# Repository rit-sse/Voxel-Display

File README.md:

RIT/SSE - Voxel Display Project
---

Society of Software Engineers' project to build a 3D display using voxels in a real 3D space.

Hi there? Are you here to try out our 3D Browser-based voxel simulator? [You can find it here.](http://rit-sse.github.io/Voxel-Display/)

The browser simulator is pretty cool - you can use your mouse and arrow keys to navigate around the 3d view. 

At first, the display is simply off. You can begin toggling voxels as you please by using the controls in the upper left.

You'll notice the "browse" button - this file selector lets you run an application with the display. Example applications can be found [in the apps folder.](https://github.com/rit-sse/Voxel-Display/tree/gh-pages/apps)

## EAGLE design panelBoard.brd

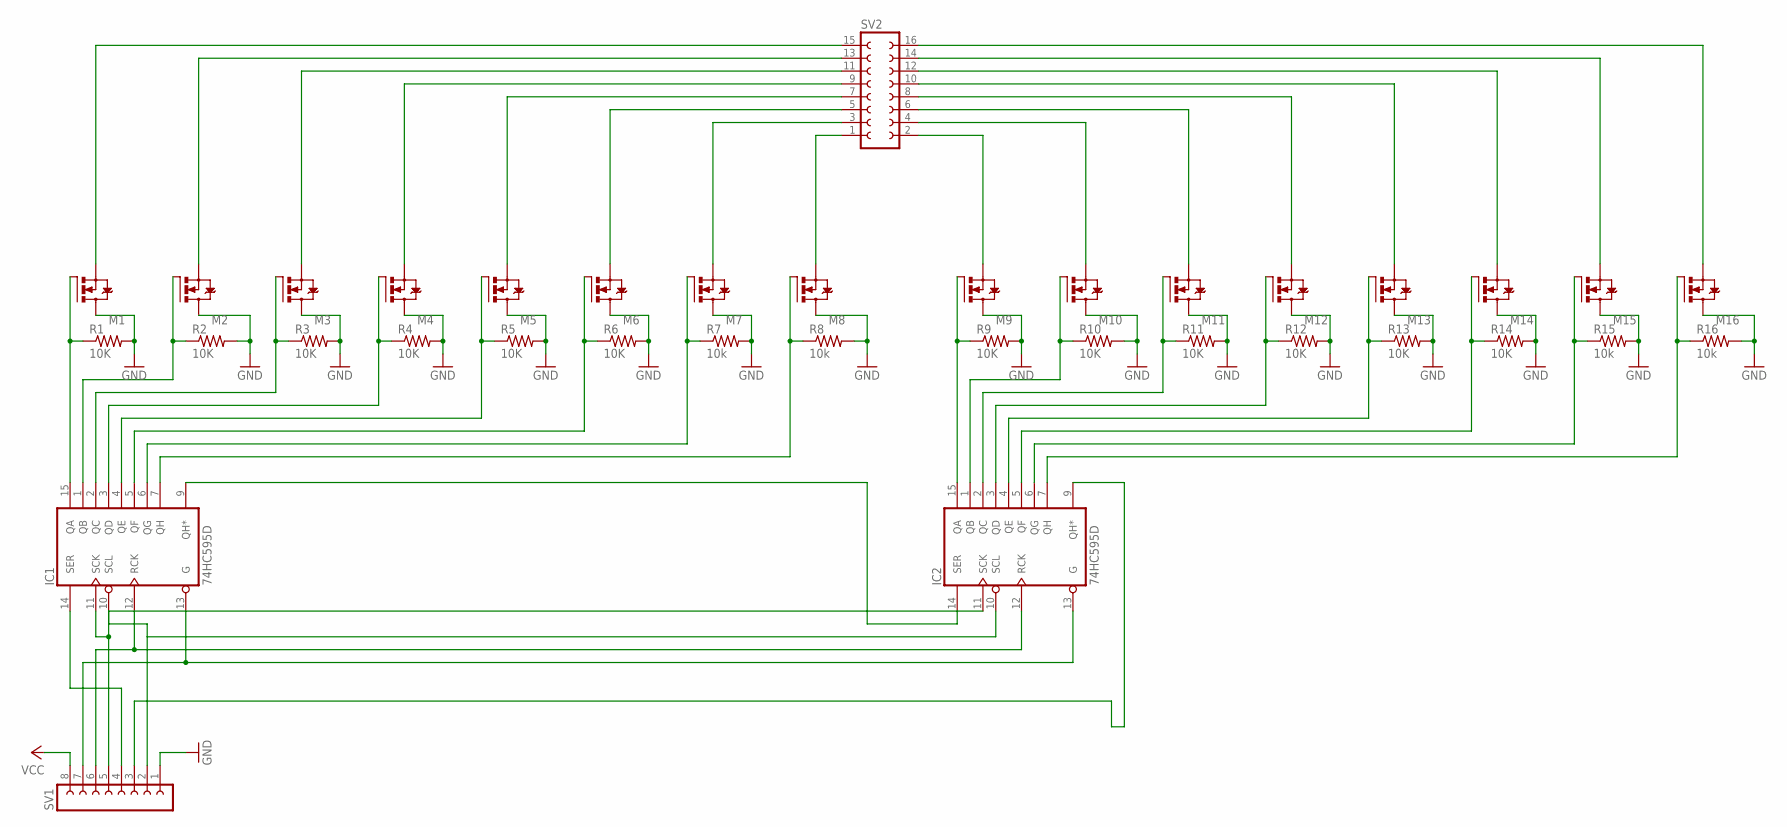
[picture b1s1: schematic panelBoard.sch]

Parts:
IC1, IC2: 74HC595D; SO16
M1, M2, M3, M4, M5, M6, M7, M8, M9, M10, M11, M12, M13, M14, M15, M16: 2N7000; TO92D-
R1, R2, R3, R4, R5, R6, R9, R10, R11, R12, R13, R14: 10K; R0603
R7, R8, R15, R16: 10k; R0603
SV1: FE08-1; FE08
SV2: FE08-2

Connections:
GND: IC1.8 (GND), IC2.8 (GND), M1.3 (D), M2.3 (D), M3.3 (D), M4.3 (D), M5.3 (D), M6.3 (D), M7.3 (D), M8.3 (D), M9.3 (D), M10.3 (D), M11.3 (D), M12.3 (D), M13.3 (D), M14.3 (D), M15.3 (D), M16.3 (D), R1.2, R2.2, R3.2, R4.2, R5.2, R6.2, R7.2, R8.2, R9.2, R10.2, R11.2, R12.2, R13.2, R14.2, R15.2, R16.2, SV1.1
unnamed: M1.1 (S), SV2.15
unnamed: M2.1 (S), SV2.13
unnamed: M3.1 (S), SV2.11
unnamed: M4.1 (S), SV2.9
unnamed: M5.1 (S), SV2.7
unnamed: M6.1 (S), SV2.5
unnamed: M7.1 (S), SV2.3
unnamed: M8.1 (S), SV2.1
unnamed: IC1.7 (QH), M8.2 (G), R8.1
unnamed: IC1.15 (QA), M1.2 (G), R1.1
unnamed: IC1.1 (QB), M2.2 (G), R2.1
unnamed: IC1.2 (QC), M3.2 (G), R3.1
unnamed: IC1.3 (QD), M4.2 (G), R4.1
unnamed: IC1.4 (QE), M5.2 (G), R5.1
unnamed: IC1.5 (QF), M6.2 (G), R6.1
unnamed: IC1.13 (G), IC2.13 (G), SV1.7
unnamed: IC1.6 (QG), M7.2 (G), R7.1
unnamed: IC1.12 (RCK), IC2.12 (RCK), SV1.6
unnamed: IC1.11 (SCK), IC2.11 (SCK), SV1.5
unnamed: IC1.14 (SER), SV1.4
unnamed: IC1.9 (QH*), IC2.14 (SER)
unnamed: IC1.10 (SCL), IC2.10 (SCL), SV1.2
unnamed: M9.1 (S), SV2.2
unnamed: M10.1 (S), SV2.4
unnamed: M11.1 (S), SV2.6
unnamed: M12.1 (S), SV2.8
unnamed: M13.1 (S), SV2.10
unnamed: M14.1 (S), SV2.12
unnamed: M15.1 (S), SV2.14
unnamed: M16.1 (S), SV2.16
unnamed: IC2.15 (QA), M9.2 (G), R9.1
unnamed: IC2.1 (QB), M10.2 (G), R10.1
unnamed: IC2.2 (QC), M11.2 (G), R11.1
unnamed: IC2.3 (QD), M12.2 (G), R12.1
unnamed: IC2.4 (QE), M13.2 (G), R13.1
unnamed: IC2.5 (QF), M14.2 (G), R14.1
unnamed: IC2.7 (QH), M16.2 (G), R16.1
unnamed: IC2.6 (QG), M15.2 (G), R15.1
unnamed: IC2.9 (QH*), SV1.3
VCC: IC1.16 (VCC), IC2.16 (VCC), SV1.8

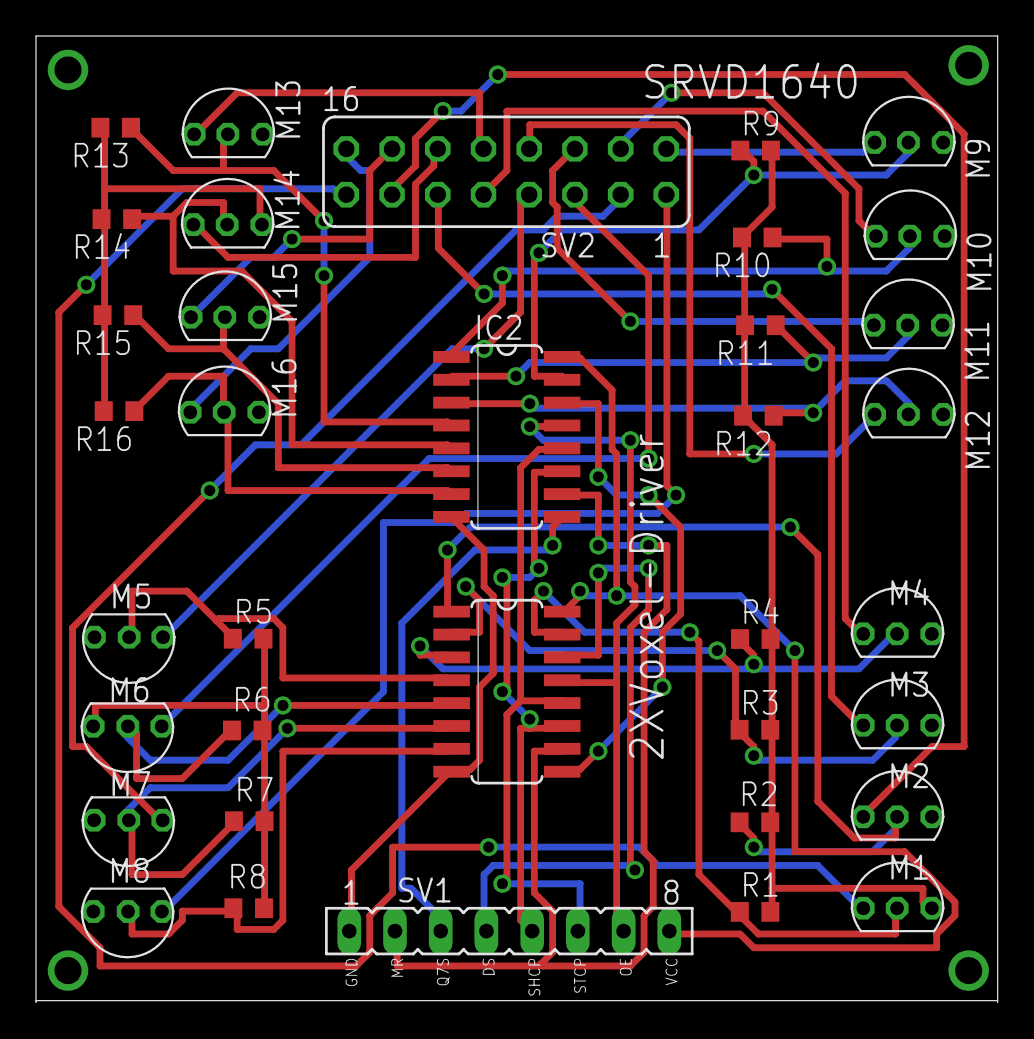
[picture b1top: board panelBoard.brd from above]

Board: 2 copper layers, 53.4 x 53.7 mm, 36 parts (0 on the bottom side), 41 nets.

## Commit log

2014-02-25 add README
2014-03-02 added Mock TkVoxelDisplay
2014-03-08 add waffle.io badge
2014-03-08 moved TkPreview to TkMockView
2014-03-08 added git ignore for TkMockView
2014-03-08 added documents for git-wiki and git-issues
2014-03-09 Added In-Progress Badge
2014-03-12 added minutes for 3_11_14
2014-03-12 updated name and refrence image
2014-03-17 Add barebones processing project
2014-03-17 Add a bunch of deps (probably more than we need)
2014-03-17 Simple 3d example
2014-03-18 added translate example, WITH COLOR\!
2014-03-18 Non-working, star code
2014-03-18 Add Voxel.scala
2014-03-19 voxel and set-voxel methods
2014-03-20 mouse controls, cleaner view
2014-03-20 new title
2014-03-20 Basic three.js renderer
2014-03-21 Add Threads.scala
2014-03-21 Remove TkMockView
2014-03-21 Text based network protocol for moxel display
2014-03-21 Simple python api example
2014-03-23 API & start of mock display
2014-03-23 Progress!
2014-03-23 parsing states are pretty done
2014-03-24 Seperated example from api, made python3x compliant
2014-03-24 created example-apps folder
2014-03-24 New python API with example
2014-03-24 Added instructions to run examples
2014-03-24 added snake code/ example
2014-03-25 Ruby pocket-api and example!
2014-03-25 renamed example
2014-03-25 empty screen fix
2014-03-25 ruby api and example update (check the empty screen state)
2014-03-25 Fix buffer bug
2014-03-25 new wave example
2014-03-25 ripple example
2014-03-25 interactive example
2014-03-25 Move Embedded to its own class
2014-03-25 Fix issue with moxel-view startup
    call app.redraw in main so you don't have to redraw the window
    when you start the app
2014-03-25 Allow sequential connections and message checking in Threads
2014-03-25 Remove print statements
2014-03-26 updated examples, blinking voxel support in mock-voxel and ruby-api
2014-03-26 updated python examples, added blinking support to python_pocket-api
2014-03-26 updated APIs
2014-03-26 added mouse click to move view (by default it doesn't move
2014-03-26 reworded title
2014-03-27 More informative print statements
2014-03-28 removed blink from mock-view, moved camera closer to objects
2014-03-28 added threads and blinking to APIs
2014-03-28 better regex matching
2014-03-28 Known Bugs
2014-03-29 Progresss
2014-03-31 moved and reorganized Examples and APIs
2014-03-31 Remove pycache
2014-03-31 updated Examples to run with moved APIs
2014-03-31 Working display, woot, woot
2014-03-31 corners for mock display
2014-03-31 Orbiter control, removes skybox, replaces with fog
2014-03-31 Can now 'run' applications.
2014-03-31 New class heirarchy
2014-04-01 started code for driver
2014-04-01 exhcange x and y coordinates so we have a right-handed viewing system
2014-04-01 Little demo app-thing
2014-04-01 Add feature warnings to build
2014-04-01 More idiomatic scala in Threads.scala
2014-04-01 Fix feature warnings in MoxelDisplay.scala
2014-04-01 re-oriented the display
2014-04-02 So very close to Hexis!
2014-04-02 A bit more balanced game version, works pretty well.
2014-04-02 fixes links in readme
2014-04-02 correct bit organization, horizontal print (vertical print is also available
2014-04-06 Moxel Display now works in the correct coords and groups
2014-04-08 Added a bunch of files, but they're all kinda needed
2014-04-09 Fixed mock-voxel bug
2014-04-09 postFixOps in Threads.scala
2014-04-09 Writing C API
2014-04-10 updated examples
2014-04-10 fixed positioning, removed print statements
2014-04-10 Start of serial driver
2014-04-10 (untested) C API now fully supports Linux.
2014-04-10 (untested) C API now supports Windows and should compile fine, too
2014-04-10 Merged Windows and Linux networking sections. Onto testing
2014-04-11 Adding example for C
2014-04-11 Hardware driver
2014-04-11 made write protocol easily configureable (No more magic numbers)
2014-04-14 Connection happens, but segfault
2014-04-14 Program executes successfully, working on data formatting
2014-04-16 C API kinda working sorta
2014-04-16 Removed documentation
2014-04-16 Removed binary things
2014-04-16 C Example working optimally
2014-04-16 Hardware server, if you please
2014-04-16 C examples mimic Python examples
2014-04-16 Update for microcontroller compatibility - seriously slows down app
2014-04-26 updated snake game
2014-04-26 revert to immediate writes
